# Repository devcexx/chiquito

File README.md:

# Chiquito 🤏

Chiquito is a simple, small, development board for the STM32C071 processors.

The STM32C071 processors are the only ones in the STM32C0 line that has an
internal accurate 48 MHz crystal oscillator, that allows to run the processor
with USB capabilities without the need of an external crystal. This is great for
small projects where you're looking to reduce the BOM.

## Features

- Processor: STM32C071G8U6 ([Complete specs here](https://www.st.com/en/microcontrollers-microprocessors/stm32c071g8.html))
  - ARM Cortex-M0+ core running at 48 MHz.
  - 64 Kbytes RAM.
  - 24 Kbytes RAM.
  - Communication: USART, SPI, I2C.
  - Full USB 2.0 support in Host and Device mode, without external oscillator.
- Integrated voltage regulator from 5V to 3.3V, up to 1A.
- Direct VBUS pin, for USB connection detection.
- 5V pin for external power supply.
- 3V3 pin for external power supply, bypassing integrated voltage regulator.
- Exposed SWD debugging interface.
- Power-on LED.

*Image pinout is a simplification. Check the original datasheet for the [complete information](https://www.st.com/resource/en/datasheet/stm32c071g8.pdf)*
## Fabrication

Production files are available in the [production](production/) folder.
Fabrication has been tested with JLCPCB, therefore it is the recommended way to
go.

Since JLCPCB prices are the same for 2 and 4 layer board, this design uses a 4
layer board where both inner layers are just ground planes, for better control
of the signal integrity and USB impedance matching. Other providers may price
you more for this number of layers.

Before sending to fabrication, always make sure that all the production files,
BOM and PCBA positioning files are correct and up-to-date. As a hobby project,
no responsability is taken for failures in the fabrication process or in the
behavior of the final board.

## Quick start

### First USB connection

By default, on the first connection, the device should boot into DFU mode.

If you don't have handy a ST-Link programmer and you're planning to use DFU as
your main way for uploading new firmware, you must use the
[STM32CubeProgrammer](https://www.st.com/en/development-tools/stm32cubeprog.html)
and set to 0 the nBOOT_SEL option **before** uploading any firmware, so you can
enter into DFU mode by just driving the BOOT0 pin low. Otherwise, after the
first firmware upload, you won't be able to access the DFU mode unless you own a
ST-Link programmer.

### Uploading new firmware

You may use either the STM32 DFU mode or an ST-link programmer to upload new
firmware:
 - By default, entering into DFU will require you to manually set the nBOOT0 pin
   to 1 using a ST-Link programmer, and then reboot the device. You may change
   this behavior by setting the nBOOT_SEL option to 0, so you can enter into DFU
   mode by just driving the BOOT0 pin low.
 
 - For using a ST-Link programmer, connect the it to the debugging pins located
   at the bottom of the board (`GND`, `SWDIO`, `SWDCLK` and `+3V3`).

## Resources

- [STM32C071G8 datasheet](https://www.st.com/resource/en/datasheet/stm32c071g8.pdf).
- [STM32C071 reference manual](https://www.st.com/resource/en/reference_manual/rm0490-stm32c0-series-advanced-armbased-32bit-mcus-stmicroelectronics.pdf).

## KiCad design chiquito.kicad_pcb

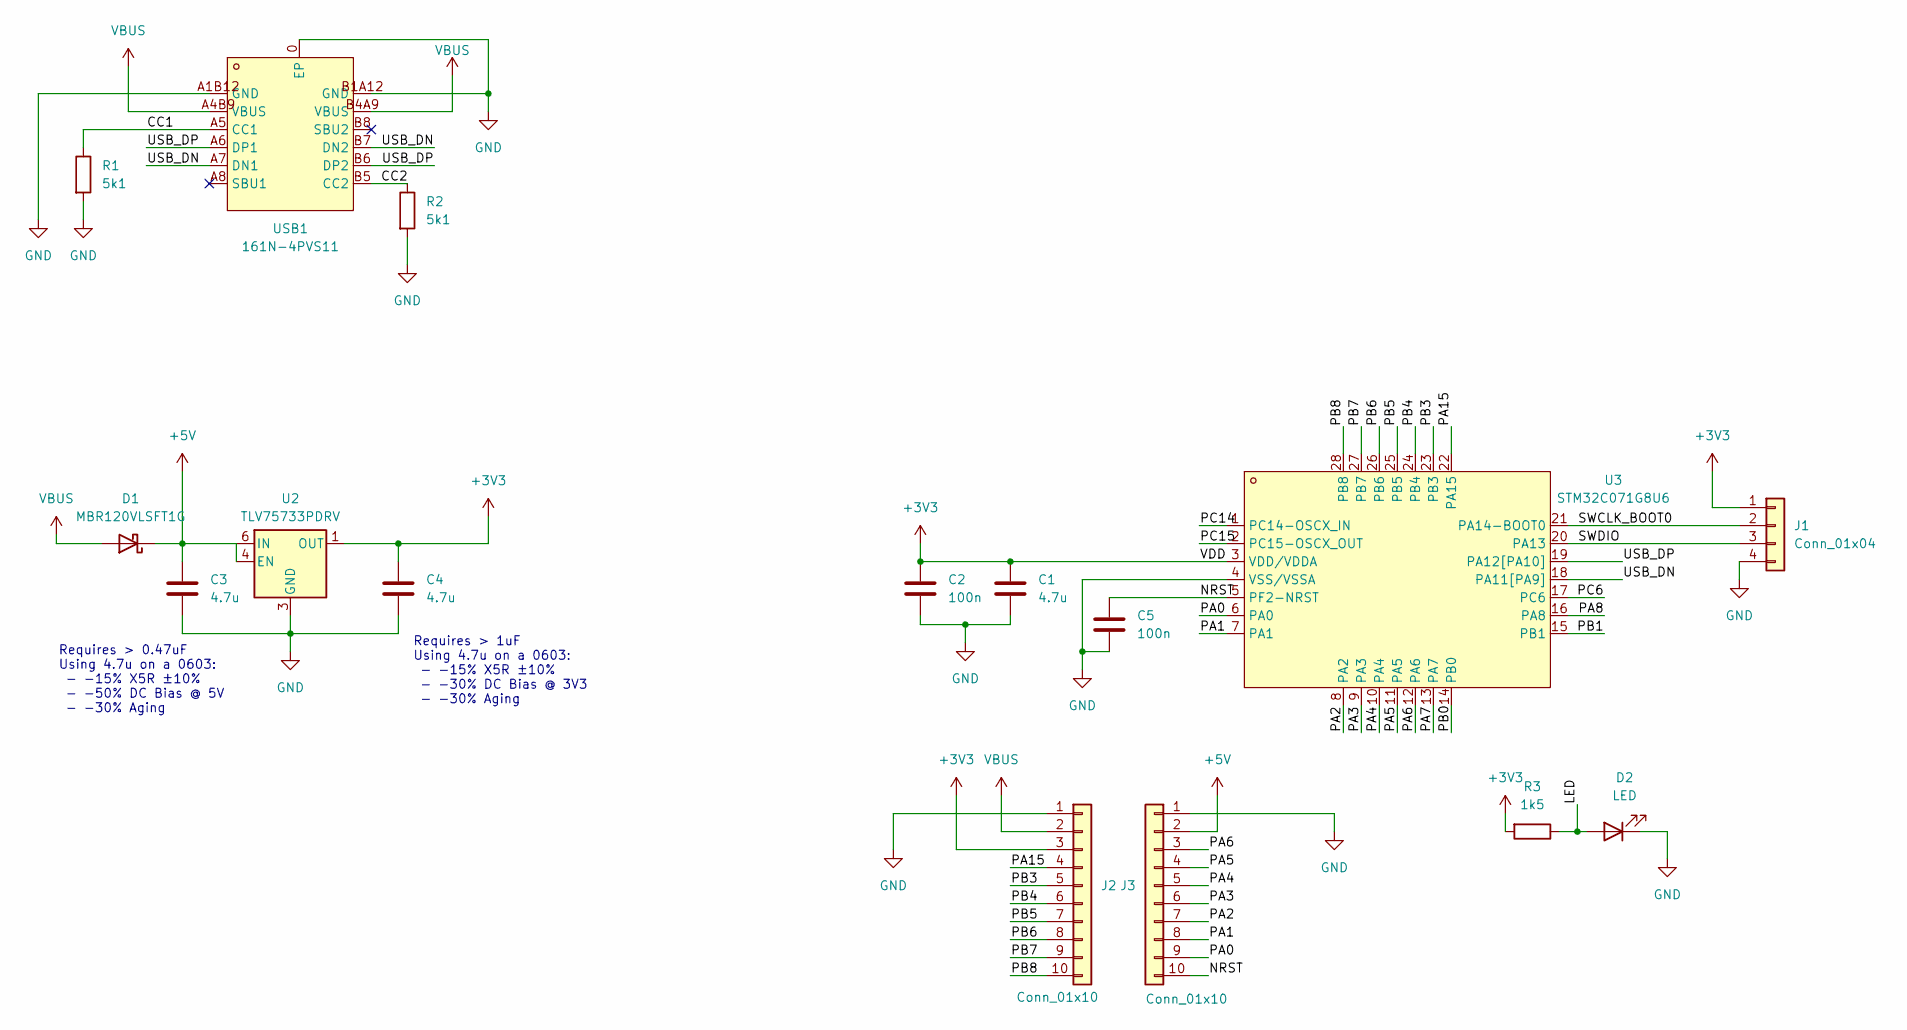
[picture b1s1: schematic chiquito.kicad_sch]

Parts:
C1: 4.7u; C_0805_2012Metric; LCSC C1779
C2, C5: 100n; C_0402_1005Metric; LCSC C1525
C3, C4: 4.7u; C_0603_1608Metric; LCSC C19666
D1: MBR120VLSFT1G; SOD-123F_L2.8-W1.8-LS3.7-RD; LCSC C191023
D2: LED; LED_0402_1005Metric; LCSC C130724
J1: Conn_01x04; PinHeader_1x04_P2.54mm_Vertical_Slim
J2, J3: Conn_01x10; PinHeader_1x10_P2.54mm_Vertical_Slim
R1, R2: 5k1; R_0402_1005Metric; LCSC C25905
R3: 1k5; R_0402_1005Metric
U2: TLV75733PDRV; WSON-6-1EP_2x2mm_P0.65mm_EP1x1.6mm; LCSC C2868428
U3: STM32C071G8U6; QFN-28_4x4mm_P0.5mm; MPN STM32C071G8U6; LCSC Part C44521811
USB1: 161N-4PVS11; USB-C-SMD_HANELECTRICITY_161N-4XVS11; MPN 161N-4PVS11; LCSC Part C5440757

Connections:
+3V3: C1.1, C2.1, C4.1, J1.1, J2.3, R3.2, U2.1 (OUT), U3.3 (VDD/VDDA)
+5V: C3.1, D1.1 (K), J3.2, U2.4 (EN), U2.6 (IN)
/CC1: R1.1, USB1.A5 (CC1)
/CC2: R2.1, USB1.B5 (CC2)
/LED: D2.2 (A), R3.1
/NRST: C5.1, J3.10, U3.5 (PF2-NRST)
/PA0: J3.9, U3.6 (PA0)
/PA1: J3.8, U3.7 (PA1)
/PA2: J3.7, U3.8 (PA2)
/PA3: J3.6, U3.9 (PA3)
/PA4: J3.5, U3.10 (PA4)
/PA5: J3.4, U3.11 (PA5)
/PA6: J3.3, U3.12 (PA6)
/PA7: U3.13 (PA7)
/PA8: U3.16 (PA8)
/PA15: J2.4, U3.22 (PA15)
/PB0: U3.14 (PB0)
/PB1: U3.15 (PB1)
/PB3: J2.5, U3.23 (PB3)
/PB4: J2.6, U3.24 (PB4)
/PB5: J2.7, U3.25 (PB5)
/PB6: J2.8, U3.26 (PB6)
/PB7: J2.9, U3.27 (PB7)
/PB8: J2.10, U3.28 (PB8)
/PC6: U3.17 (PC6)
/PC14: U3.1 (PC14-OSCX_IN)
/PC15: U3.2 (PC15-OSCX_OUT)
/SWCLK_BOOT0: J1.2, U3.21 (PA14-BOOT0)
/SWDIO: J1.3, U3.20 (PA13)
/USB_DN: U3.18 (PA11[PA9]), USB1.A7 (DN1), USB1.B7 (DN2)
/USB_DP: U3.19 (PA12[PA10]), USB1.A6 (DP1), USB1.B6 (DP2)
GND: C1.2, C2.2, C3.2, C4.2, C5.2, D2.1 (K), J1.4, J2.1, J3.1, R1.2, R2.2, U2.3 (GND), U2.7 (GND), U3.4 (VSS/VSSA), USB1.0 (EP), USB1.A1B12 (GND), USB1.B1A12 (GND)
VBUS: D1.2 (A), J2.2, USB1.A4B9 (VBUS), USB1.B4A9 (VBUS)

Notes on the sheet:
Requires > 0.47uF Using 4.7u on a 0603: - -15% X5R ±10% - -50% DC Bias @ 5V - -30% Aging
Requires > 1uF Using 4.7u on a 0603: - -15% X5R ±10% - -30% DC Bias @ 3V3 - -30% Aging

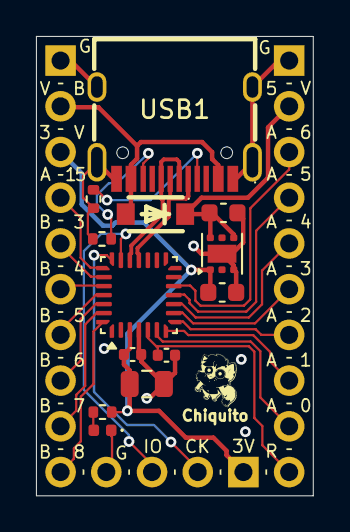
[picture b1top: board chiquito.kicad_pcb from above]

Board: 4 copper layers, 15.4 x 25.5 mm, 16 parts (0 on the bottom side), 26 nets.
